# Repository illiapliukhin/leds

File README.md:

# leds

LED matrix / wearable LED electronics, firmware and tools.

## Where things live
- **mono_electronics v15 (ESP32-S3 mono LED driver board, PR #4): standalone KiCad project, fab outputs, drawings, renders and docs in [`projects/mono_electronics_v15/`](projects/mono_electronics_v15/).** This is the canonical copy to open and order from.
- Working sources: `hardware/mono_schematic/` (schematic and generator tools), `hardware/mono_electronics/` (board, review docs); fab history in `manufacturing/mono_electronics/` (v11b–v15).
- Interface standard: `hardware/common/LED_INTERFACE_STANDARD.md`.
- Firmware: `firmware/`. Simulators and analysis: `tools/`, `leds_analysis/`.

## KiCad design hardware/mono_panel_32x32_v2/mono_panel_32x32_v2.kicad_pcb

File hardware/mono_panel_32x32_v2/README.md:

# mono_panel_32x32_v2 — 32×32 white 2835 LED panel, 8 mm pitch, 256×256 mm

This is a single-colour matrix panel for `projects/mono_electronics_v15`, following `hardware/common/LED_INTERFACE_STANDARD.md`.
- J_ROW1 and J_COL1 are Hirose FH12-40S-0.5SH on B.Cu, mid-board. Pin 1 is north; the cable exits west when viewed from the back. Use a 40-way 0.5 mm FFC, Type B (pin 1 → pin 1), ≤200 mm.
- J_ROW: 35/36 ID_SDA/SCL, 37 ID_3V3, 33/38/39/40 GND, 34 NC.
- U_ID1 is an M24C02 EEPROM at address 0x50.
- Six M2 NPTH holes, 2.2 mm (use nylon screws/standoffs). Fiducials 3 + 3.
- Edge-to-first-LED distance is 4.0 mm = pitch/2, so panels tile edge-to-edge with a continuous 8 mm pitch.
- See TRADE_STUDY.md for the LED choice and cost.

| Gate (KiCad 10.0.7) | Result |
|---|---|
| ERC (all severities) | 0 |
| DRC (all severities) | 0 |
| Unconnected | 0 |
| Schematic parity | 0 |

Rules (in `.kicad_pro`) and stackup:
- 0.127 mm minimum clearance; tracks ≥0.15 mm; vias 0.6/0.3; edge 0.3 mm.
- Stackup JLC04161H-7628, 1.6 mm, 1 oz outer.
- Every bend is a tangent arc: router output is string-pulled to any-angle straight runs (bilinear distance-field line of sight, 0.15 mm clearance), then filleted; `check_bends.py` audits tangency. GND zones on In2/B.Cu use thermal reliefs (0.3 gap / 0.3 spoke) and are refilled before plotting. 455 GND stitching vias.

## Row drop (docs/analysis.json, from the routed copper)
- Load: 32 LEDs × 10 mA = 0.32 A per row.
- Copper: ρ +20% (60 °C / plating). The bus is modelled as distributed load fed from the worst end.
- Worst case is ROW_01:
  - board ≈ 75 mV (1.0 mm bus ≈ 0.46 Ω/2, plus fan-out and via)
  - plus 200 mm FFC 1.64 Ω/m and 2 contacts ≈ 124 mV
  - **total ≈ 199 mV, under the 350 mV budget.**
- Worst-case headroom: 4.24 − 0.199 − 0.035 (AO3403) − 2.75 V (Vf max) ≈ 1.26 V left for the MBI5124 sink.
- IPC-2221 at ΔT 10 °C: 0.3 mm external ≈ 1.0 A; 1.0 mm bus ≈ 2.4 A; 0.2 mm internal ≈ 0.37 A.
  - These compare against 0.32 A peak / 57 mA RMS (1/32 duty), so heating is negligible.

## Build
- `./build.sh`: schematic → PCB base → maze router → arcs/zones → ERC/DRC/parity.
- `./make_fab.sh`: zone refill, gerbers + drill, `fab/BOM_JLC.csv`, `fab/CPL_JLC.csv`, zip.
- `python3.11 analyze.py`: row-drop analysis.

## JLC
- Upload `fab/mono_panel_32x32_v2_gerbers.zip`: 4 layers, 1.6 mm, impedance stackup JLC04161H-7628.
- PCBA both sides, using BOM_JLC.csv and CPL_JLC.csv.
- Parts: C2843876 ×1024, C202114 ×2, C7562, C1525. All were in stock on 2026-10-12.

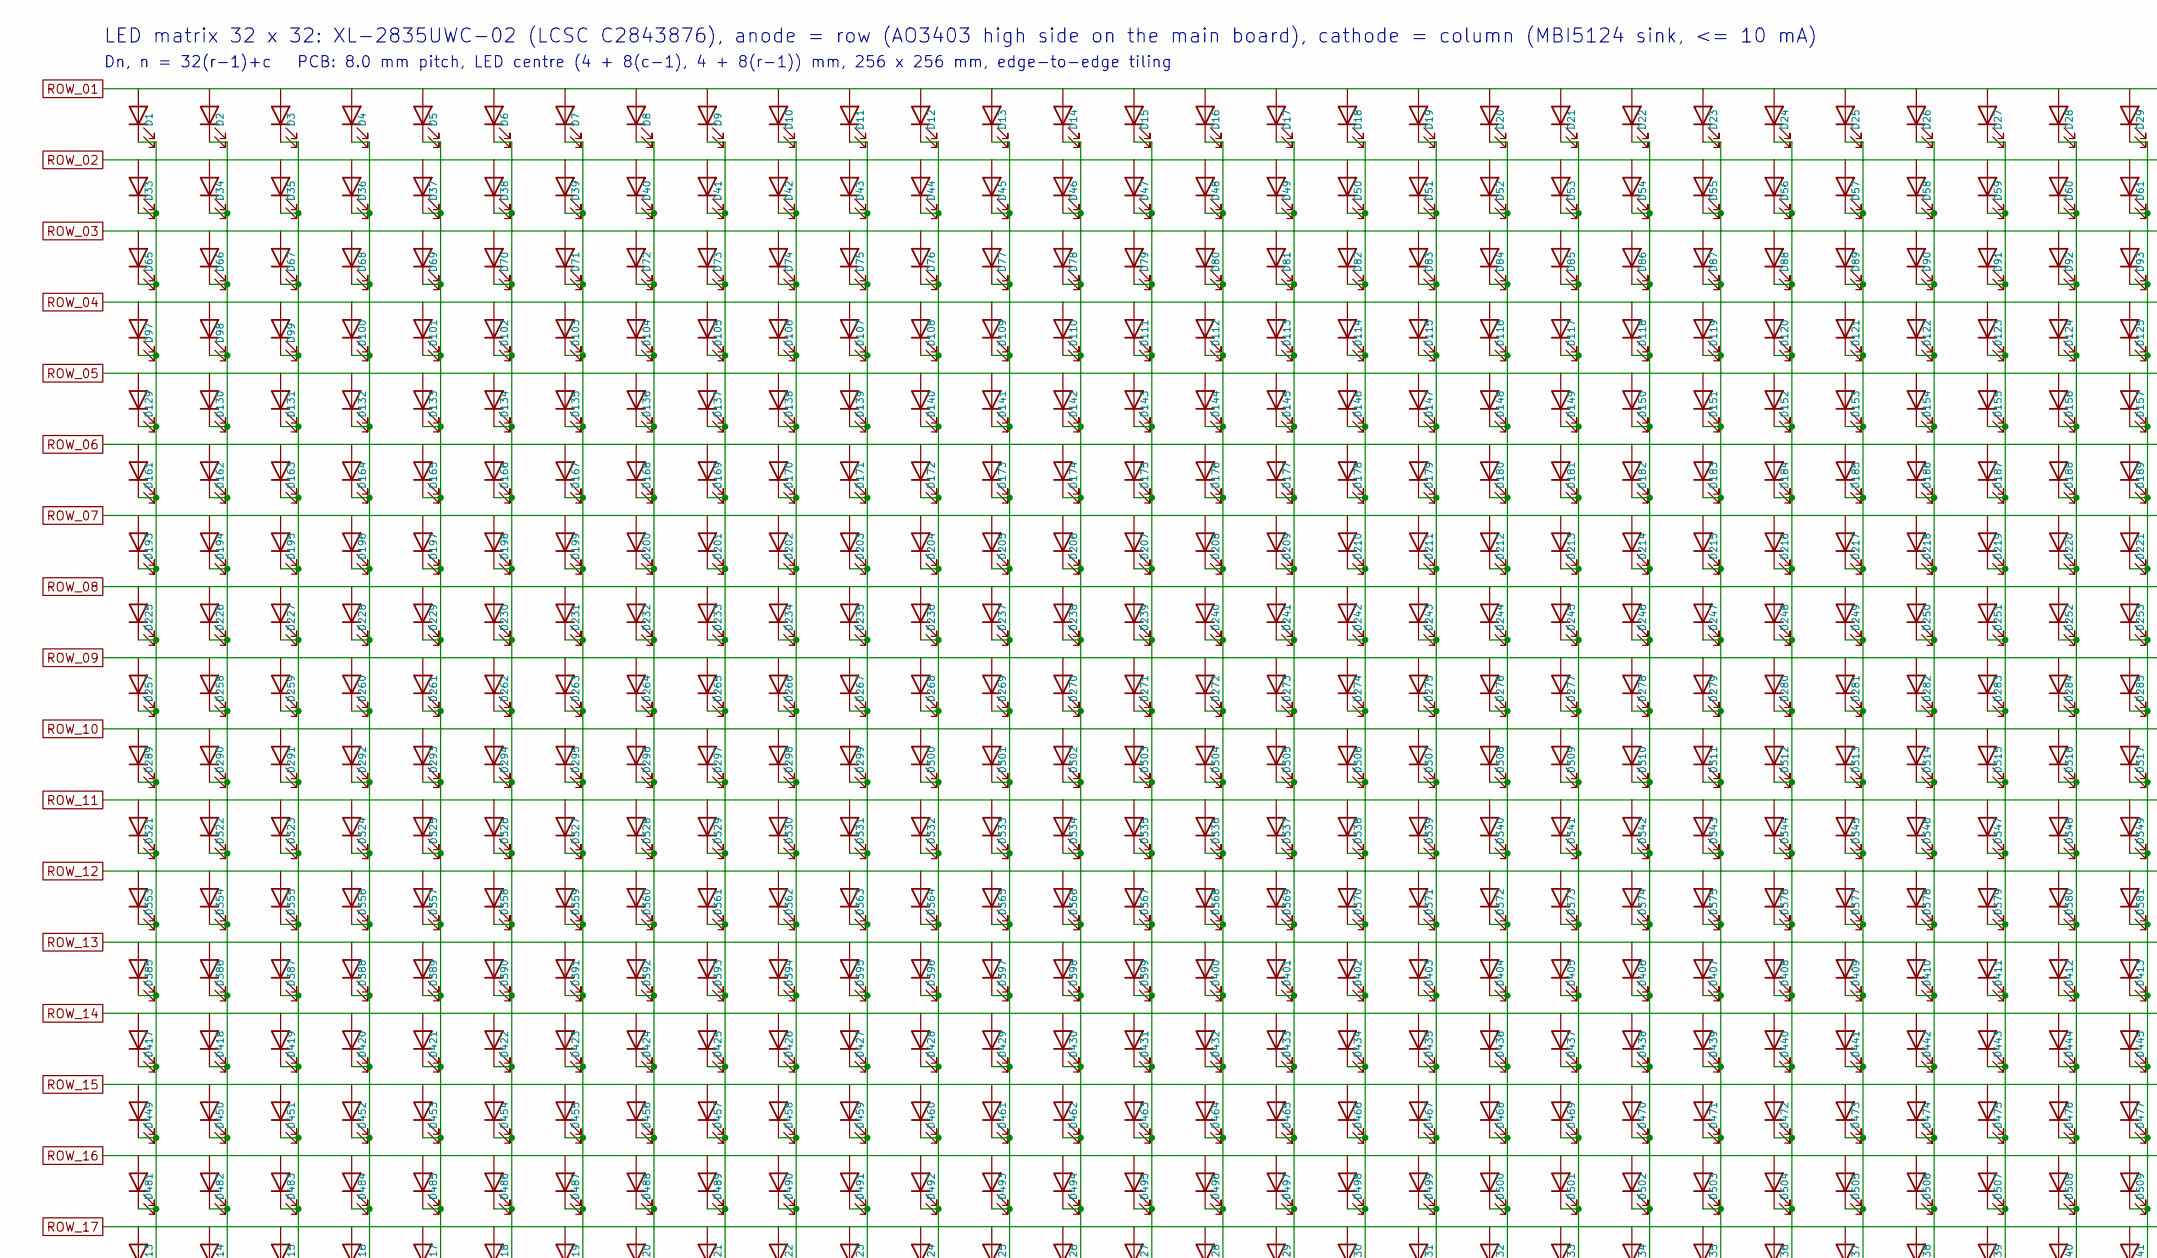
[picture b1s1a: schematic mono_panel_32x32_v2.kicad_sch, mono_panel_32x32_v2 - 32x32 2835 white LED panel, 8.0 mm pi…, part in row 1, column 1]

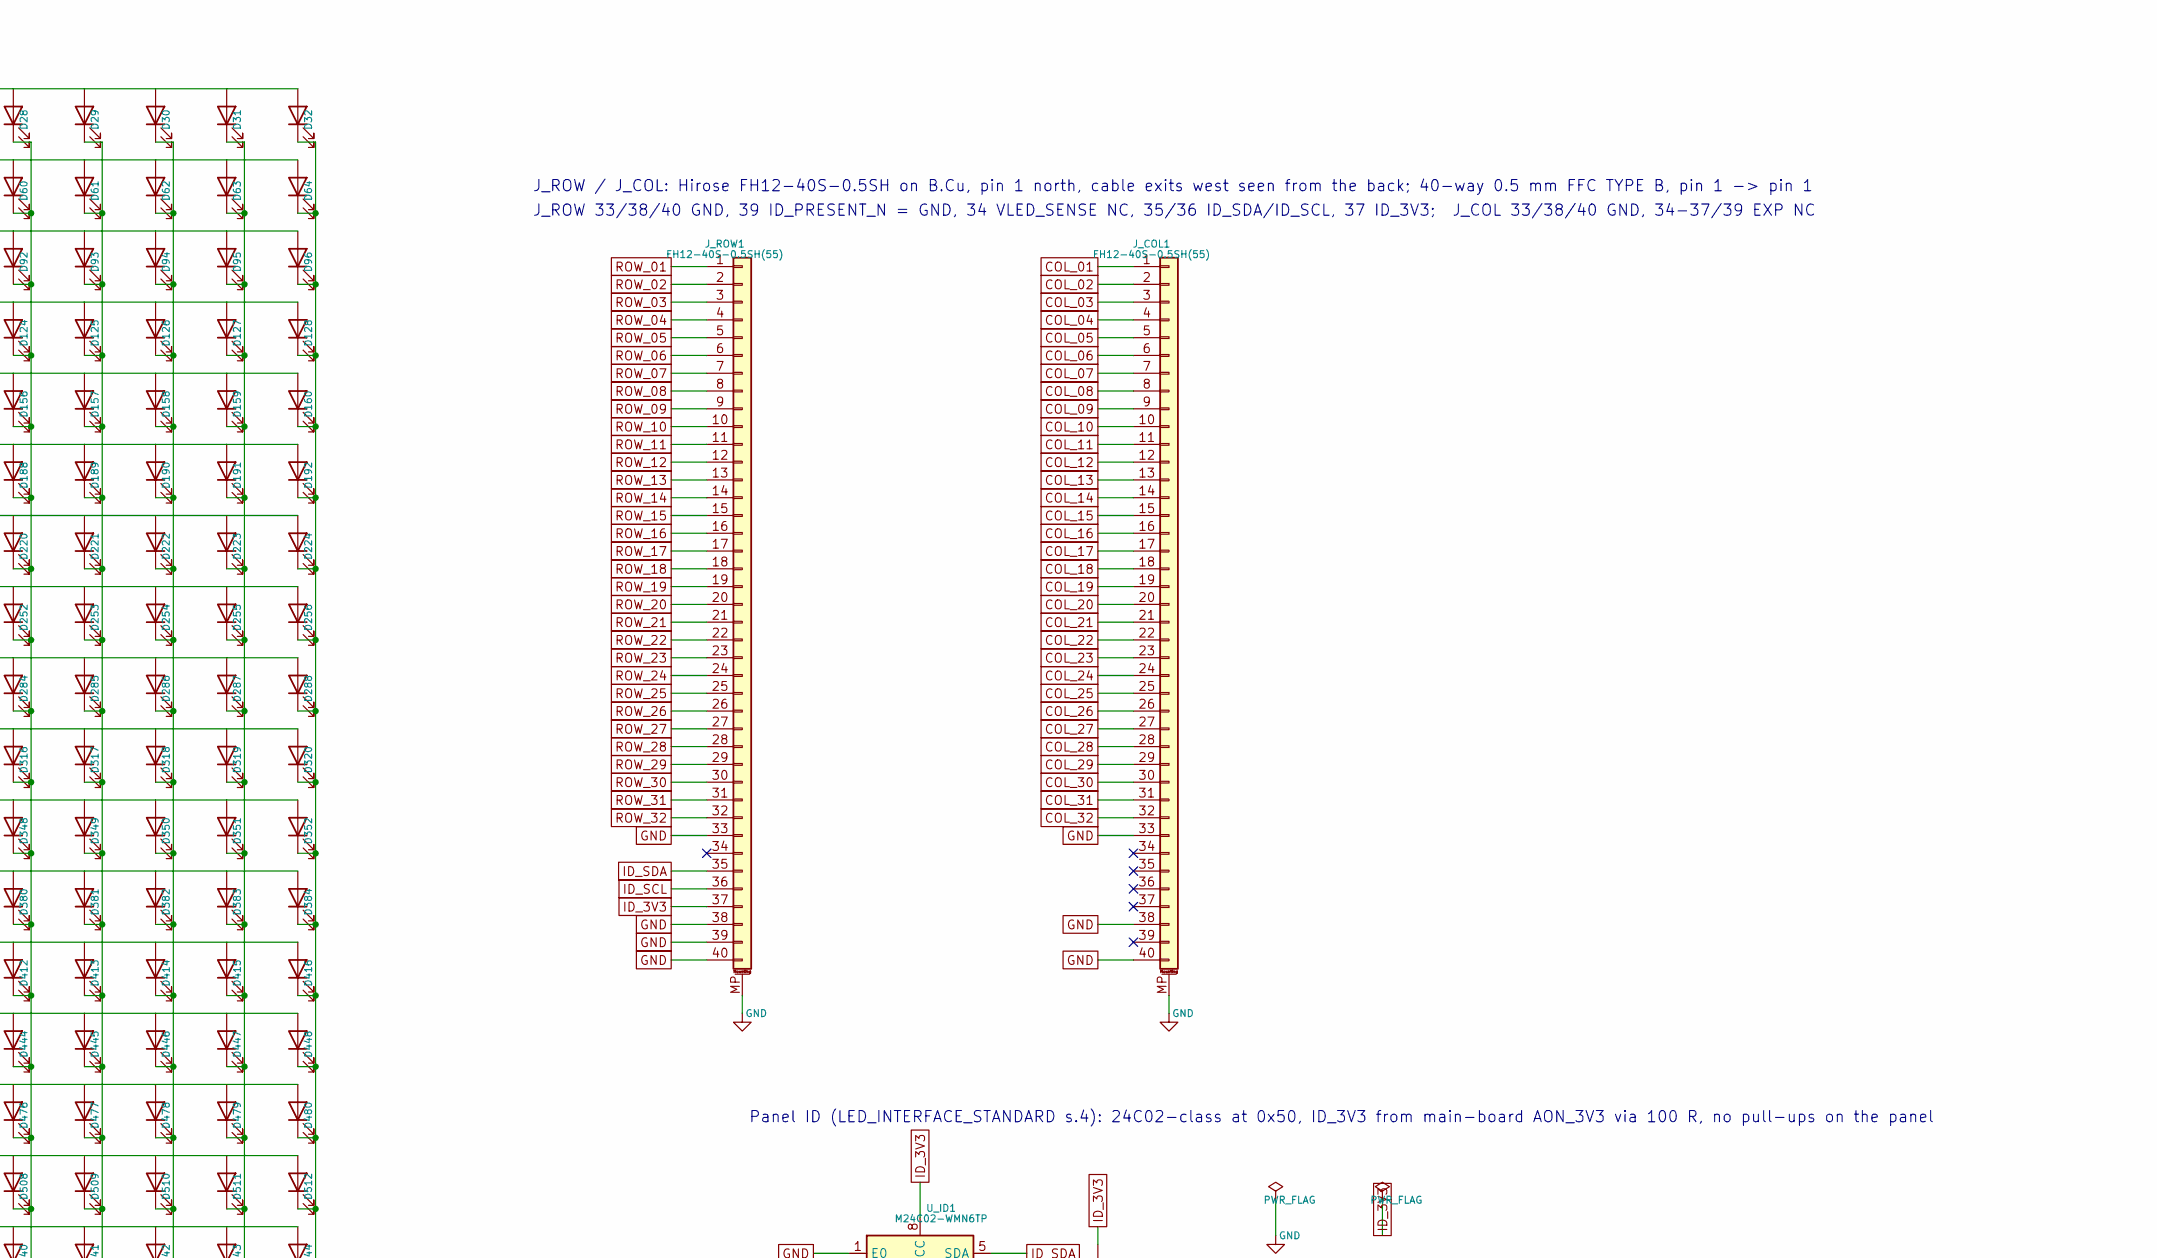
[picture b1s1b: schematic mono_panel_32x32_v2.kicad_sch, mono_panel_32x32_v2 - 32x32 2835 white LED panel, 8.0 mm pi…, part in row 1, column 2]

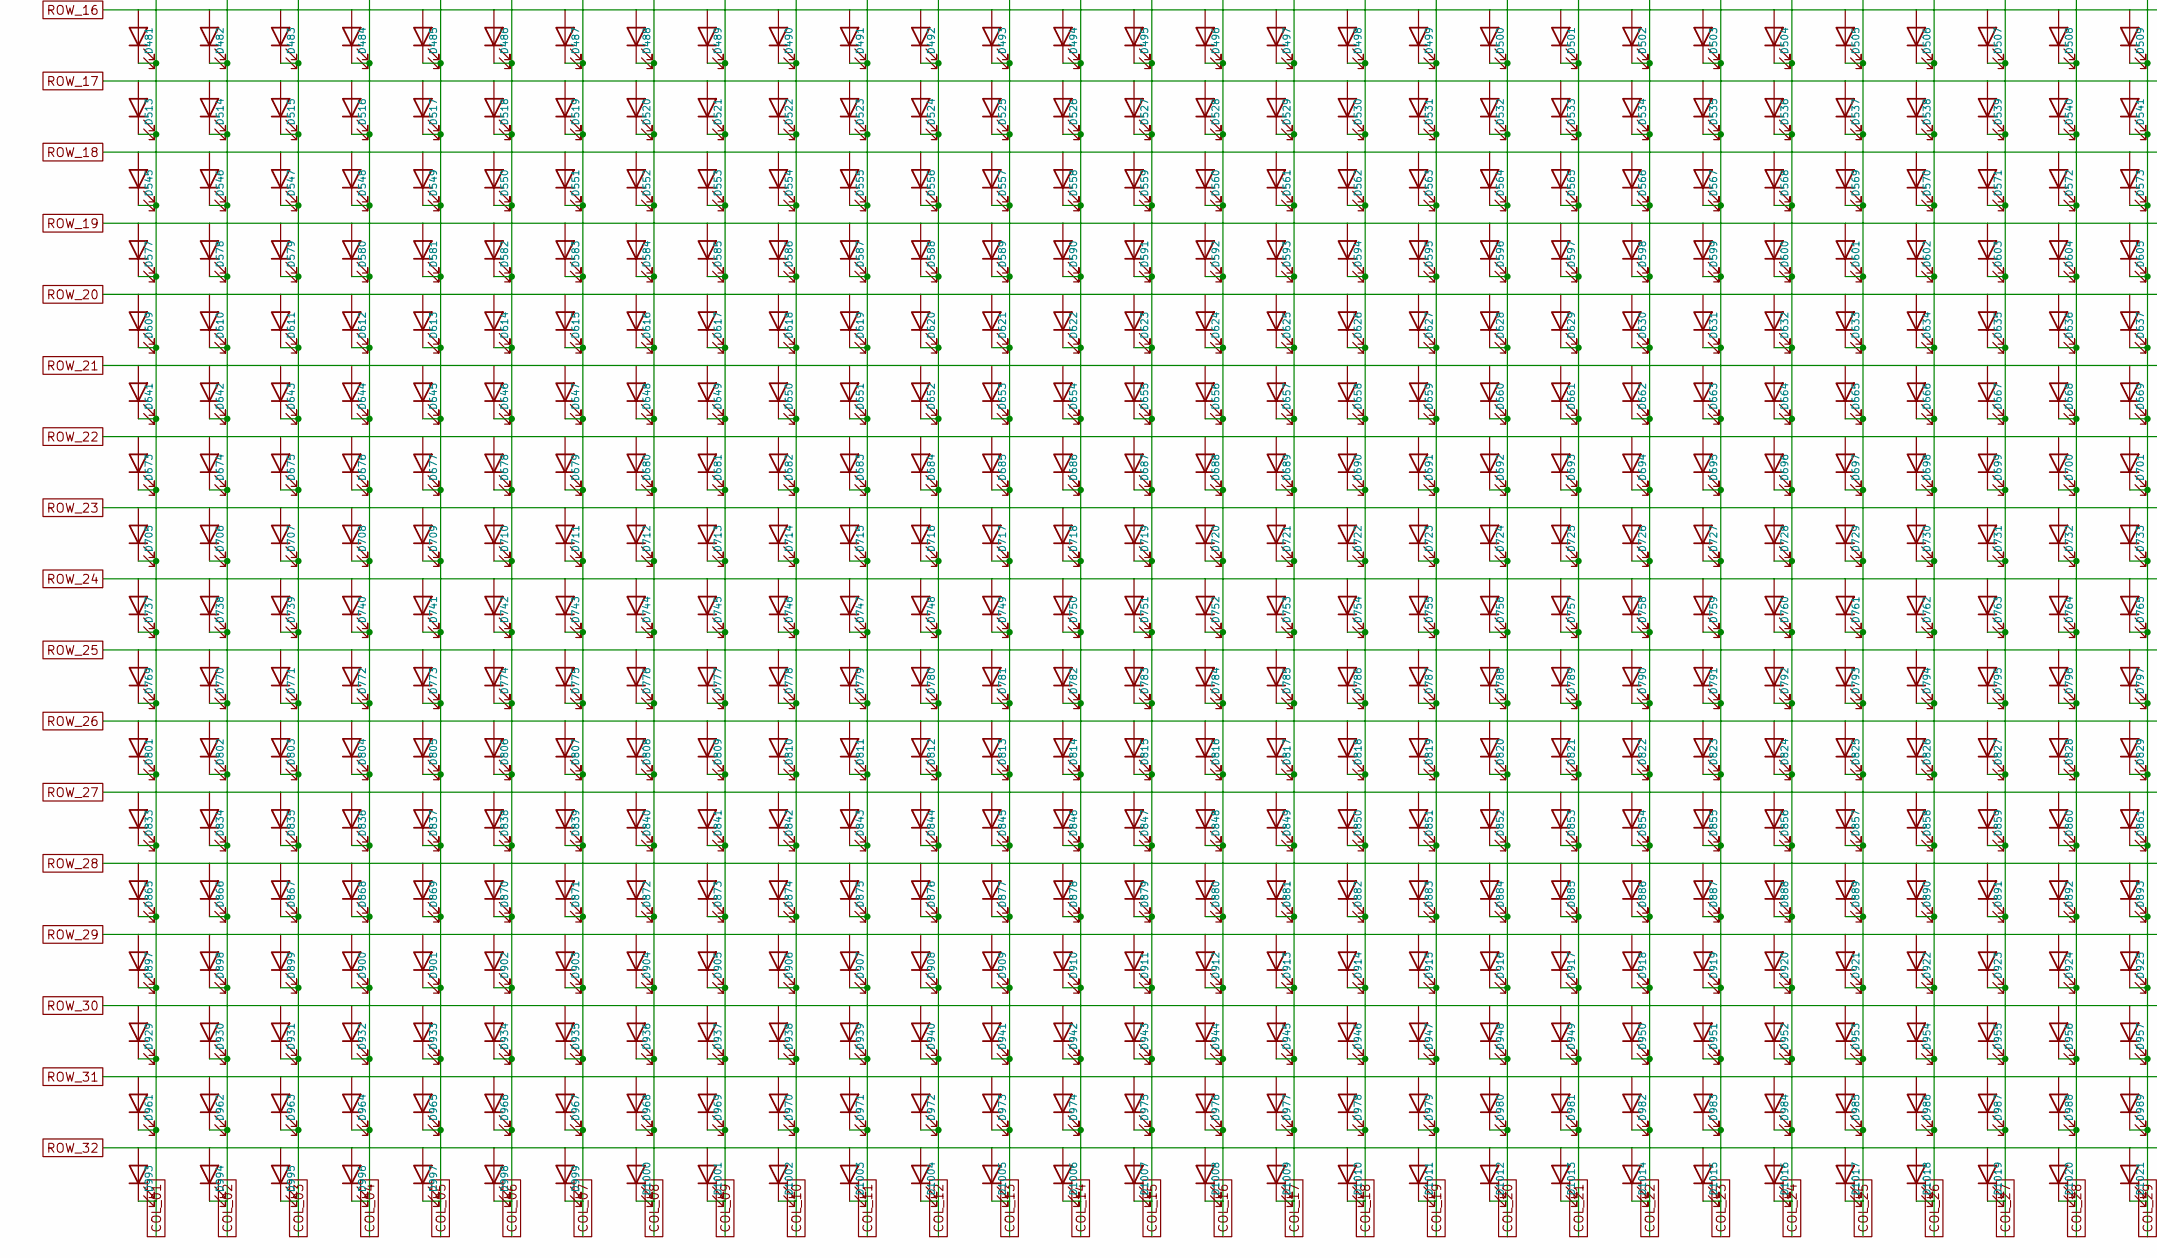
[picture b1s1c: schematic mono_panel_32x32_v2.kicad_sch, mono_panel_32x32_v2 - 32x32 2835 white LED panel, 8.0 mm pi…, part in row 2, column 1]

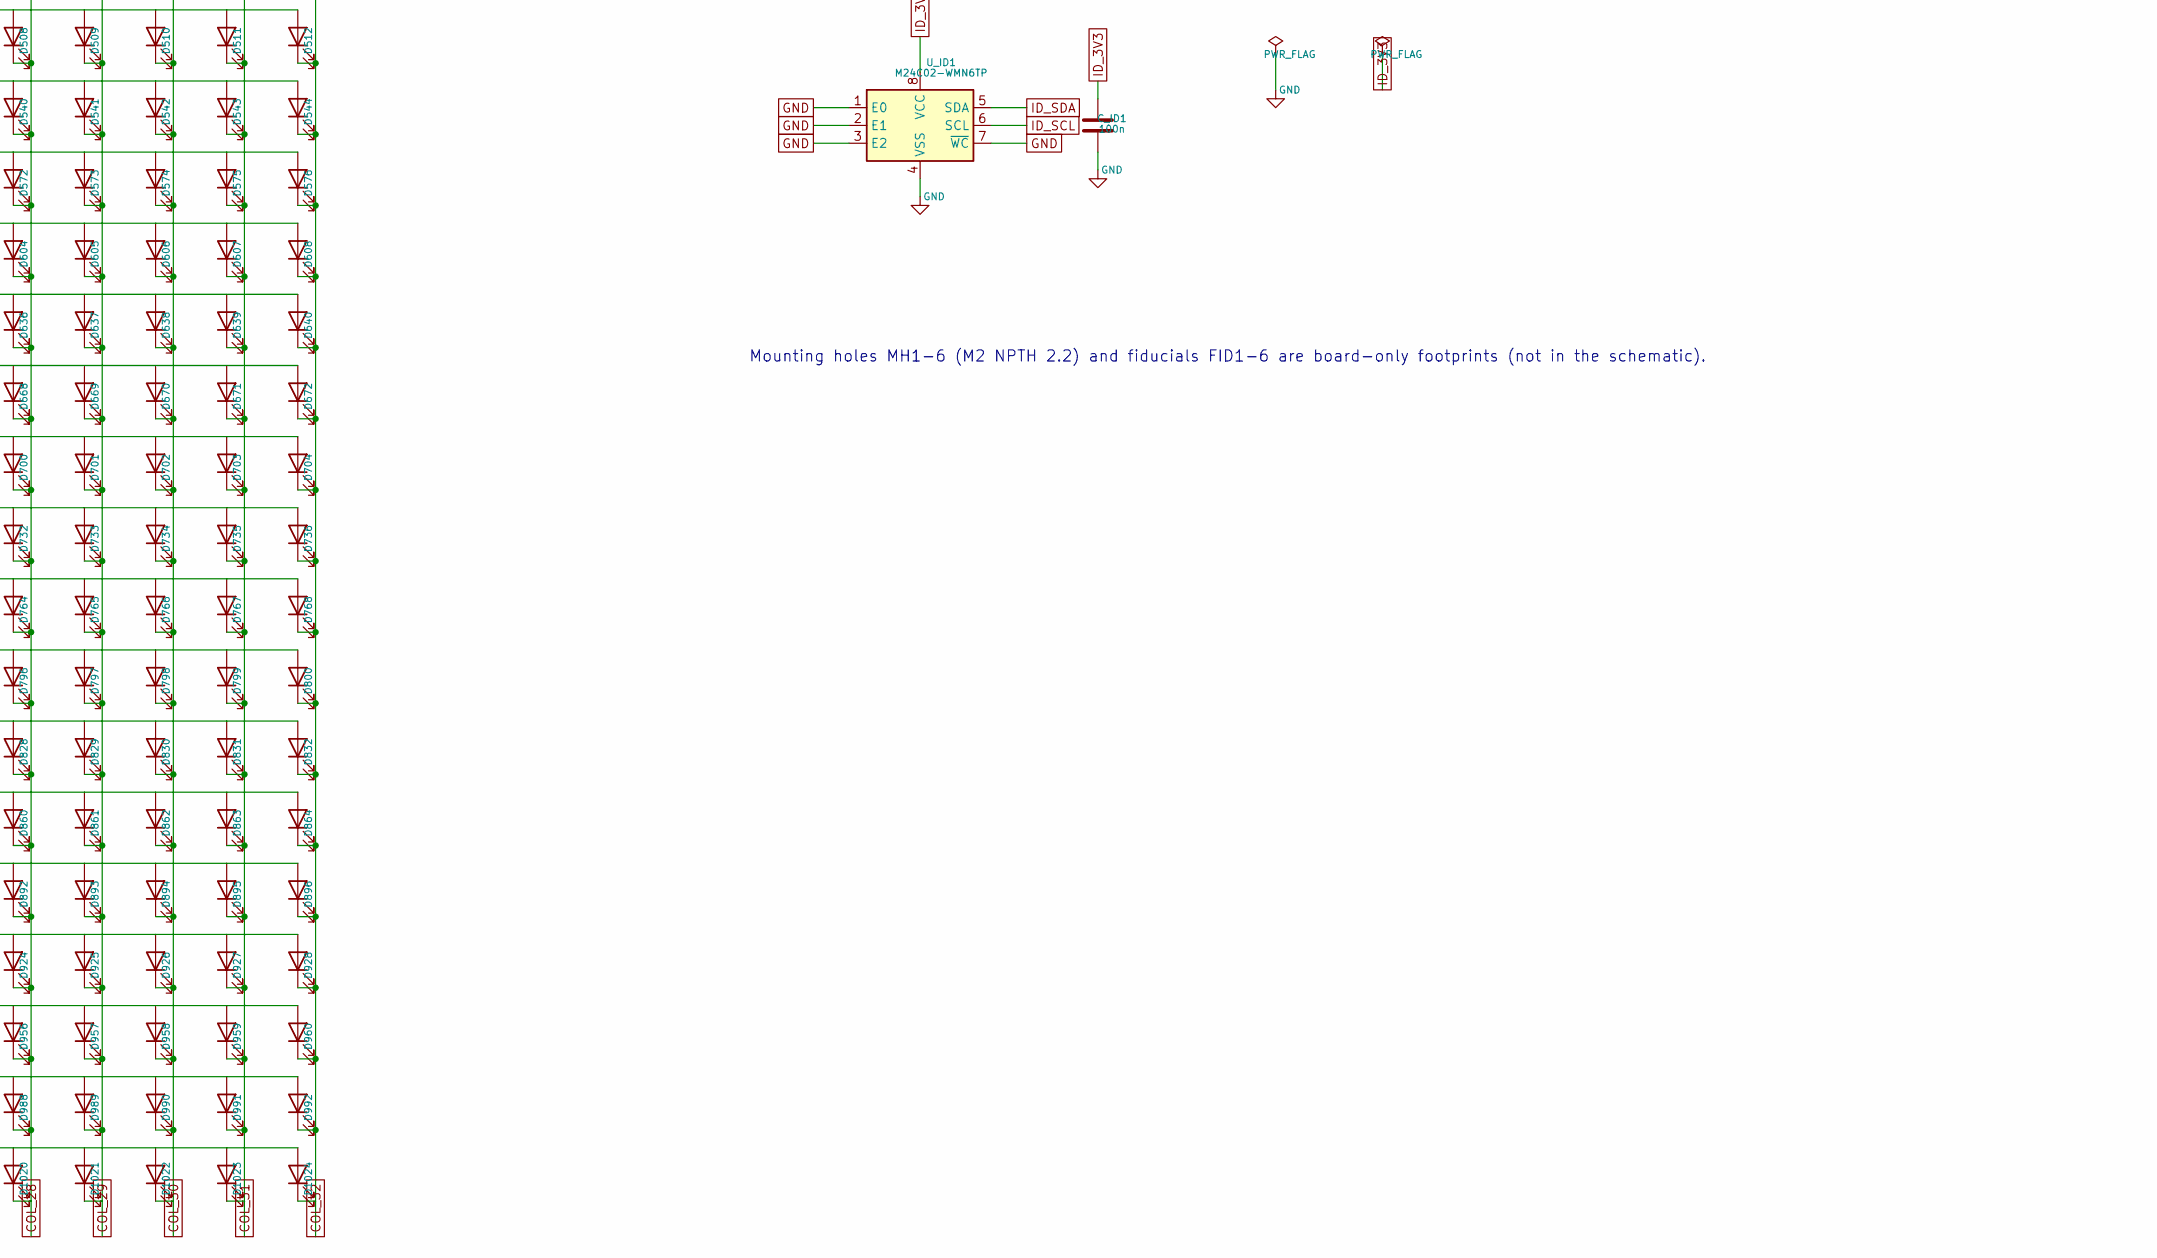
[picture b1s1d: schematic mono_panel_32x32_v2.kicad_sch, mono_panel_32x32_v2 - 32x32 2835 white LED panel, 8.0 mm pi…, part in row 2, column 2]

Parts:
C_ID1: 100n; C_0402_1005Metric; MPN Samsung CL05B104KO5NNNC; LCSC C1525
D1, D2, D3, D4, D5, D6, D7, D8, D9, D10, D11, D12, D13, D14, D15, D16, D17, D18, D19, D20, D21, D22, D23, D24, D25, D26, D27, D28, D29, D30, D31, D32, D33, D34, D35, D36, D37, D38, D39, D40, D41, D42, D43, D44, D45, D46, D47, D48, D49, D50, D51, D52, D53, D54, D55, D56, D57, D58, D59, D60, D61, D62, D63, D64, D65, D66, D67, D68, D69, D70, D71, D72, D73, D74, D75, D76, D77, D78, D79, D80, D81, D82, D83, D84, D85, D86, D87, D88, D89, D90, D91, D92, D93, D94, D95, D96, D97, D98, D99, D100, D101, D102, D103, D104, D105, D106, D107, D108, D109, D110, D111, D112, D113, D114, D115, D116, D117, D118, D119, D120, D121, D122, D123, D124, D125, D126, D127, D128, D129, D130, D131, D132, D133, D134, D135, D136, D137, D138, D139, D140, D141, D142, D143, D144, D145, D146, D147, D148, D149, D150, D151, D152, D153, D154, D155, D156, D157, D158, D159, D160, D161, D162, D163, D164, D165, D166, D167, D168, D169, D170, D171, D172, D173, D174, D175, D176, D177, D178, D179, D180, D181, D182, D183, D184, D185, D186, D187, D188, D189, D190, D191, D192, D193, D194, D195, D196, D197, D198, D199, D200, D201, D202, D203, D204, D205, D206, D207, D208, D209, D210, D211, D212, D213, D214, D215, D216, D217, D218, D219, D220, D221, D222, D223, D224, D225, D226, D227, D228, D229, D230, D231, D232, D233, D234, D235, D236, D237, D238, D239, D240, D241, D242, D243, D244, D245, D246, D247, D248, D249, D250, D251, D252, D253, D254, D255, D256, D257, D258, D259, D260, D261, D262, D263, D264, D265, D266, D267, D268, D269, D270, D271, D272, D273, D274, D275, D276, D277, D278, D279, D280, D281, D282, D283, D284, D285, D286, D287, D288, D289, D290, D291, D292, D293, D294, D295, D296, D297, D298, D299, D300, D301, D302, D303, D304, D305, D306, D307, D308, D309, D310, D311, D312, D313, D314, D315, D316, D317, D318, D319, D320, D321, D322, D323, D324, D325, D326, D327, D328, D329, D330, D331, D332, D333, D334, D335, D336, D337, D338, D339, D340, D341, D342, D343, D344, D345, D346, D347, D348, D349, D350, D351, D352, D353, D354, D355, D356, D357, D358, D359, D360, D361, D362, D363, D364, D365, D366, D367, D368, D369, D370, D371, D372, D373, D374, D375, D376, D377, D378, D379, D380, D381, D382, D383, D384, D385, D386, D387, D388, D389, D390, D391, D392, D393, D394, D395, D396, D397, D398, D399, D400, D401, D402, D403, D404, D405, D406, D407, D408, D409, D410, D411, D412, D413, D414, D415, D416, D417, D418, D419, D420, D421, D422, D423, D424, D425, D426, D427, D428, D429, D430, D431, D432, D433, D434, D435, D436, D437, D438, D439, D440, D441, D442, D443, D444, D445, D446, D447, D448, D449, D450, D451, D452, D453, D454, D455, D456, D457, D458, D459, D460, D461, D462, D463, D464, D465, D466, D467, D468, D469, D470, D471, D472, D473, D474, D475, D476, D477, D478, D479, D480, D481, D482, D483, D484, D485, D486, D487, D488, D489, D490, D491, D492, D493, D494, D495, D496, D497, D498, D499, D500, D501, D502, D503, D504, D505, D506, D507, D508, D509, D510, D511, D512, D513, D514, D515, D516, D517, D518, D519, D520, D521, D522, D523, D524, D525, D526, D527, D528, D529, D530, D531, D532, D533, D534, D535, D536, D537, D538, D539, D540, D541, D542, D543, D544, D545, D546, D547, D548, D549, D550, D551, D552, D553, D554, D555, D556, D557, D558, D559, D560, D561, D562, D563, D564, D565, D566, D567, D568, D569, D570, D571, D572, D573, D574, D575, D576, D577, D578, D579, D580, D581, D582, D583, D584, D585, D586, D587, D588, D589, D590, D591, D592, D593, D594, D595, D596, D597, D598, D599, D600, D601, D602, D603, D604, D605, D606, D607, D608, D609, D610, D611, D612, D613, D614, D615, D616, D617, D618, D619, D620, D621, D622, D623, D624, D625, D626, D627, D628, D629, D630, D631, D632, D633, D634, D635, D636, D637, D638, D639, D640, D641, D642, D643, D644, D645, D646, D647, D648, D649, D650, D651, D652, D653, D654, D655, D656, D657, D658, D659, D660, D661, D662, D663, D664, D665, D666, D667, D668, D669, D670, D671, D672, D673, D674, D675, D676, D677, D678, D679, D680, D681, D682, D683, D684, D685, D686, D687, D688, D689, D690, D691, D692, D693, D694, D695, D696, D697, D698, D699, D700, D701, D702, D703, D704, D705, D706, D707, D708, D709, D710, D711, D712, D713, D714, D715, D716, D717, D718, D719, D720, D721, D722, D723, D724, D725, D726, D727, D728, D729, D730, D731, D732, D733, D734, D735, D736, D737, D738, D739, D740, D741, D742, D743, D744, D745, D746, D747, D748, D749, D750, D751, D752, D753, D754, D755, D756, D757, D758, D759, D760, D761, D762, D763, D764, D765, D766, D767, D768, D769, D770, D771, D772, D773, D774, D775, D776, D777, D778, D779, D780, D781, D782, D783, D784, D785, D786, D787, D788, D789, D790, D791, D792, D793, D794, D795, D796, D797, D798, D799, D800, D801, D802, D803, D804, D805, D806, D807, D808, D809, D810, D811, D812, D813, D814, D815, D816, D817, D818, D819, D820, D821, D822, D823, D824, D825, D826, D827, D828, D829, D830, D831, D832, D833, D834, D835, D836, D837, D838, D839, D840, D841, D842, D843, D844, D845, D846, D847, D848, D849, D850, D851, D852, D853, D854, D855, D856, D857, D858, D859, D860, D861, D862, D863, D864, D865, D866, D867, D868, D869, D870, D871, D872, D873, D874, D875, D876, D877, D878, D879, D880, D881, D882, D883, D884, D885, D886, D887, D888, D889, D890, D891, D892, D893, D894, D895, D896, D897, D898, D899, D900, D901, D902, D903, D904, D905, D906, D907, D908, D909, D910, D911, D912, D913, D914, D915, D916, D917, D918, D919, D920, D921, D922, D923, D924, D925, D926, D927, D928, D929, D930, D931, D932, D933, D934, D935, D936, D937, D938, D939, D940, D941, D942, D943, D944, D945, D946, D947, D948, D949, D950, D951, D952, D953, D954, D955, D956, D957, D958, D959, D960, D961, D962, D963, D964, D965, D966, D967, D968, D969, D970, D971, D972, D973, D974, D975, D976, D977, D978, D979, D980, D981, D982, D983, D984, D985, D986, D987, D988, D989, D990, D991, D992, D993, D994, D995, D996, D997, D998, D999, D1000, D1001, D1002, D1003, D1004, D1005, D1006, D1007, D1008, D1009, D1010, D1011, D1012, D1013, D1014, D1015, D1016, D1017, D1018, D1019, D1020, D1021, D1022, D1023, D1024: XL-2835UWC-02; LED_2835_XL-2835UWC; MPN XINGLIGHT XL-2835UWC-02; LCSC C2843876
J_COL1: FH12-40S-0.5SH(55); Hirose_FH12-40S-0.5SH_B; MPN Hirose FH12-40S-0.5SH(55); LCSC C202114
J_ROW1: FH12-40S-0.5SH(55); Hirose_FH12-40S-0.5SH_B; MPN Hirose FH12-40S-0.5SH(55); LCSC C202114
U_ID1: M24C02-WMN6TP; SOIC-8_3.9x4.9mm_P1.27mm; MPN ST M24C02-WMN6TP; LCSC C7562

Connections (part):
COL_01: D1.1 (K), D33.1 (K), D65.1 (K), D97.1 (K), D129.1 (K), D161.1 (K), D193.1 (K), D225.1 (K), D257.1 (K), D289.1 (K), D321.1 (K), D353.1 (K), D385.1 (K), D417.1 (K), D449.1 (K), D481.1 (K), D513.1 (K), D545.1 (K), D577.1 (K), D609.1 (K), D641.1 (K), D673.1 (K), D705.1 (K), D737.1 (K), D769.1 (K), D801.1 (K), D833.1 (K), D865.1 (K), D897.1 (K), D929.1 (K), D961.1 (K), D993.1 (K), J_COL1.1
COL_02: D2.1 (K), D34.1 (K), D66.1 (K), D98.1 (K), D130.1 (K), D162.1 (K), D194.1 (K), D226.1 (K), D258.1 (K), D290.1 (K), D322.1 (K), D354.1 (K), D386.1 (K), D418.1 (K), D450.1 (K), D482.1 (K), D514.1 (K), D546.1 (K), D578.1 (K), D610.1 (K), D642.1 (K), D674.1 (K), D706.1 (K), D738.1 (K), D770.1 (K), D802.1 (K), D834.1 (K), D866.1 (K), D898.1 (K), D930.1 (K), D962.1 (K), D994.1 (K), J_COL1.2
COL_03: D3.1 (K), D35.1 (K), D67.1 (K), D99.1 (K), D131.1 (K), D163.1 (K), D195.1 (K), D227.1 (K), D259.1 (K), D291.1 (K), D323.1 (K), D355.1 (K), D387.1 (K), D419.1 (K), D451.1 (K), D483.1 (K), D515.1 (K), D547.1 (K), D579.1 (K), D611.1 (K), D643.1 (K), D675.1 (K), D707.1 (K), D739.1 (K), D771.1 (K), D803.1 (K), D835.1 (K), D867.1 (K), D899.1 (K), D931.1 (K), D963.1 (K), D995.1 (K), J_COL1.3
COL_04: D4.1 (K), D36.1 (K), D68.1 (K), D100.1 (K), D132.1 (K), D164.1 (K), D196.1 (K), D228.1 (K), D260.1 (K), D292.1 (K), D324.1 (K), D356.1 (K), D388.1 (K), D420.1 (K), D452.1 (K), D484.1 (K), D516.1 (K), D548.1 (K), D580.1 (K), D612.1 (K), D644.1 (K), D676.1 (K), D708.1 (K), D740.1 (K), D772.1 (K), D804.1 (K), D836.1 (K), D868.1 (K), D900.1 (K), D932.1 (K), D964.1 (K), D996.1 (K), J_COL1.4
COL_05: D5.1 (K), D37.1 (K), D69.1 (K), D101.1 (K), D133.1 (K), D165.1 (K), D197.1 (K), D229.1 (K), D261.1 (K), D293.1 (K), D325.1 (K), D357.1 (K), D389.1 (K), D421.1 (K), D453.1 (K), D485.1 (K), D517.1 (K), D549.1 (K), D581.1 (K), D613.1 (K), D645.1 (K), D677.1 (K), D709.1 (K), D741.1 (K), D773.1 (K), D805.1 (K), D837.1 (K), D869.1 (K), D901.1 (K), D933.1 (K), D965.1 (K), D997.1 (K), J_COL1.5
COL_06: D6.1 (K), D38.1 (K), D70.1 (K), D102.1 (K), D134.1 (K), D166.1 (K), D198.1 (K), D230.1 (K), D262.1 (K), D294.1 (K), D326.1 (K), D358.1 (K), D390.1 (K), D422.1 (K), D454.1 (K), D486.1 (K), D518.1 (K), D550.1 (K), D582.1 (K), D614.1 (K), D646.1 (K), D678.1 (K), D710.1 (K), D742.1 (K), D774.1 (K), D806.1 (K), D838.1 (K), D870.1 (K), D902.1 (K), D934.1 (K), D966.1 (K), D998.1 (K), J_COL1.6
COL_07: D7.1 (K), D39.1 (K), D71.1 (K), D103.1 (K), D135.1 (K), D167.1 (K), D199.1 (K), D231.1 (K), D263.1 (K), D295.1 (K), D327.1 (K), D359.1 (K), D391.1 (K), D423.1 (K), D455.1 (K), D487.1 (K), D519.1 (K), D551.1 (K), D583.1 (K), D615.1 (K), D647.1 (K), D679.1 (K), D711.1 (K), D743.1 (K), D775.1 (K), D807.1 (K), D839.1 (K), D871.1 (K), D903.1 (K), D935.1 (K), D967.1 (K), D999.1 (K), J_COL1.7
COL_08: D8.1 (K), D40.1 (K), D72.1 (K), D104.1 (K), D136.1 (K), D168.1 (K), D200.1 (K), D232.1 (K), D264.1 (K), D296.1 (K), D328.1 (K), D360.1 (K), D392.1 (K), D424.1 (K), D456.1 (K), D488.1 (K), D520.1 (K), D552.1 (K), D584.1 (K), D616.1 (K), D648.1 (K), D680.1 (K), D712.1 (K), D744.1 (K), D776.1 (K), D808.1 (K), D840.1 (K), D872.1 (K), D904.1 (K), D936.1 (K), D968.1 (K), D1000.1 (K), J_COL1.8
COL_09: D9.1 (K), D41.1 (K), D73.1 (K), D105.1 (K), D137.1 (K), D169.1 (K), D201.1 (K), D233.1 (K), D265.1 (K), D297.1 (K), D329.1 (K), D361.1 (K), D393.1 (K), D425.1 (K), D457.1 (K), D489.1 (K), D521.1 (K), D553.1 (K), D585.1 (K), D617.1 (K), D649.1 (K), D681.1 (K), D713.1 (K), D745.1 (K), D777.1 (K), D809.1 (K), D841.1 (K), D873.1 (K), D905.1 (K), D937.1 (K), D969.1 (K), D1001.1 (K), J_COL1.9
COL_10: D10.1 (K), D42.1 (K), D74.1 (K), D106.1 (K), D138.1 (K), D170.1 (K), D202.1 (K), D234.1 (K), D266.1 (K), D298.1 (K), D330.1 (K), D362.1 (K), D394.1 (K), D426.1 (K), D458.1 (K), D490.1 (K), D522.1 (K), D554.1 (K), D586.1 (K), D618.1 (K), D650.1 (K), D682.1 (K), D714.1 (K), D746.1 (K), D778.1 (K), D810.1 (K), D842.1 (K), D874.1 (K), D906.1 (K), D938.1 (K), D970.1 (K), D1002.1 (K), J_COL1.10
COL_11: D11.1 (K), D43.1 (K), D75.1 (K), D107.1 (K), D139.1 (K), D171.1 (K), D203.1 (K), D235.1 (K), D267.1 (K), D299.1 (K), D331.1 (K), D363.1 (K), D395.1 (K), D427.1 (K), D459.1 (K), D491.1 (K), D523.1 (K), D555.1 (K), D587.1 (K), D619.1 (K), D651.1 (K), D683.1 (K), D715.1 (K), D747.1 (K), D779.1 (K), D811.1 (K), D843.1 (K), D875.1 (K), D907.1 (K), D939.1 (K), D971.1 (K), D1003.1 (K), J_COL1.11
COL_12: D12.1 (K), D44.1 (K), D76.1 (K), D108.1 (K), D140.1 (K), D172.1 (K), D204.1 (K), D236.1 (K), D268.1 (K), D300.1 (K), D332.1 (K), D364.1 (K), D396.1 (K), D428.1 (K), D460.1 (K), D492.1 (K), D524.1 (K), D556.1 (K), D588.1 (K), D620.1 (K), D652.1 (K), D684.1 (K), D716.1 (K), D748.1 (K), D780.1 (K), D812.1 (K), D844.1 (K), D876.1 (K), D908.1 (K), D940.1 (K), D972.1 (K), D1004.1 (K), J_COL1.12
COL_13: D13.1 (K), D45.1 (K), D77.1 (K), D109.1 (K), D141.1 (K), D173.1 (K), D205.1 (K), D237.1 (K), D269.1 (K), D301.1 (K), D333.1 (K), D365.1 (K), D397.1 (K), D429.1 (K), D461.1 (K), D493.1 (K), D525.1 (K), D557.1 (K), D589.1 (K), D621.1 (K), D653.1 (K), D685.1 (K), D717.1 (K), D749.1 (K), D781.1 (K), D813.1 (K), D845.1 (K), D877.1 (K), D909.1 (K), D941.1 (K), D973.1 (K), D1005.1 (K), J_COL1.13
COL_14: D14.1 (K), D46.1 (K), D78.1 (K), D110.1 (K), D142.1 (K), D174.1 (K), D206.1 (K), D238.1 (K), D270.1 (K), D302.1 (K), D334.1 (K), D366.1 (K), D398.1 (K), D430.1 (K), D462.1 (K), D494.1 (K), D526.1 (K), D558.1 (K), D590.1 (K), D622.1 (K), D654.1 (K), D686.1 (K), D718.1 (K), D750.1 (K), D782.1 (K), D814.1 (K), D846.1 (K), D878.1 (K), D910.1 (K), D942.1 (K), D974.1 (K), D1006.1 (K), J_COL1.14
COL_15: D15.1 (K), D47.1 (K), D79.1 (K), D111.1 (K), D143.1 (K), D175.1 (K), D207.1 (K), D239.1 (K), D271.1 (K), D303.1 (K), D335.1 (K), D367.1 (K), D399.1 (K), D431.1 (K), D463.1 (K), D495.1 (K), D527.1 (K), D559.1 (K), D591.1 (K), D623.1 (K), D655.1 (K), D687.1 (K), D719.1 (K), D751.1 (K), D783.1 (K), D815.1 (K), D847.1 (K), D879.1 (K), D911.1 (K), D943.1 (K), D975.1 (K), D1007.1 (K), J_COL1.15
COL_16: D16.1 (K), D48.1 (K), D80.1 (K), D112.1 (K), D144.1 (K), D176.1 (K), D208.1 (K), D240.1 (K), D272.1 (K), D304.1 (K), D336.1 (K), D368.1 (K), D400.1 (K), D432.1 (K), D464.1 (K), D496.1 (K), D528.1 (K), D560.1 (K), D592.1 (K), D624.1 (K), D656.1 (K), D688.1 (K), D720.1 (K), D752.1 (K), D784.1 (K), D816.1 (K), D848.1 (K), D880.1 (K), D912.1 (K), D944.1 (K), D976.1 (K), D1008.1 (K), J_COL1.16
COL_17: D17.1 (K), D49.1 (K), D81.1 (K), D113.1 (K), D145.1 (K), D177.1 (K), D209.1 (K), D241.1 (K), D273.1 (K), D305.1 (K), D337.1 (K), D369.1 (K), D401.1 (K), D433.1 (K), D465.1 (K), D497.1 (K), D529.1 (K), D561.1 (K), D593.1 (K), D625.1 (K), D657.1 (K), D689.1 (K), D721.1 (K), D753.1 (K), D785.1 (K), D817.1 (K), D849.1 (K), D881.1 (K), D913.1 (K), D945.1 (K), D977.1 (K), D1009.1 (K), J_COL1.17
COL_18: D18.1 (K), D50.1 (K), D82.1 (K), D114.1 (K), D146.1 (K), D178.1 (K), D210.1 (K), D242.1 (K), D274.1 (K), D306.1 (K), D338.1 (K), D370.1 (K), D402.1 (K), D434.1 (K), D466.1 (K), D498.1 (K), D530.1 (K), D562.1 (K), D594.1 (K), D626.1 (K), D658.1 (K), D690.1 (K), D722.1 (K), D754.1 (K), D786.1 (K), D818.1 (K), D850.1 (K), D882.1 (K), D914.1 (K), D946.1 (K), D978.1 (K), D1010.1 (K), J_COL1.18
COL_19: D19.1 (K), D51.1 (K), D83.1 (K), D115.1 (K), D147.1 (K), D179.1 (K), D211.1 (K), D243.1 (K), D275.1 (K), D307.1 (K), D339.1 (K), D371.1 (K), D403.1 (K), D435.1 (K), D467.1 (K), D499.1 (K), D531.1 (K), D563.1 (K), D595.1 (K), D627.1 (K), D659.1 (K), D691.1 (K), D723.1 (K), D755.1 (K), D787.1 (K), D819.1 (K), D851.1 (K), D883.1 (K), D915.1 (K), D947.1 (K), D979.1 (K), D1011.1 (K), J_COL1.19
COL_20: D20.1 (K), D52.1 (K), D84.1 (K), D116.1 (K), D148.1 (K), D180.1 (K), D212.1 (K), D244.1 (K), D276.1 (K), D308.1 (K), D340.1 (K), D372.1 (K), D404.1 (K), D436.1 (K), D468.1 (K), D500.1 (K), D532.1 (K), D564.1 (K), D596.1 (K), D628.1 (K), D660.1 (K), D692.1 (K), D724.1 (K), D756.1 (K), D788.1 (K), D820.1 (K), D852.1 (K), D884.1 (K), D916.1 (K), D948.1 (K), D980.1 (K), D1012.1 (K), J_COL1.20
COL_21: D21.1 (K), D53.1 (K), D85.1 (K), D117.1 (K), D149.1 (K), D181.1 (K), D213.1 (K), D245.1 (K), D277.1 (K), D309.1 (K), D341.1 (K), D373.1 (K), D405.1 (K), D437.1 (K), D469.1 (K), D501.1 (K), D533.1 (K), D565.1 (K), D597.1 (K), D629.1 (K), D661.1 (K), D693.1 (K), D725.1 (K), D757.1 (K), D789.1 (K), D821.1 (K), D853.1 (K), D885.1 (K), D917.1 (K), D949.1 (K), D981.1 (K), D1013.1 (K), J_COL1.21
COL_22: D22.1 (K), D54.1 (K), D86.1 (K), D118.1 (K), D150.1 (K), D182.1 (K), D214.1 (K), D246.1 (K), D278.1 (K), D310.1 (K), D342.1 (K), D374.1 (K), D406.1 (K), D438.1 (K), D470.1 (K), D502.1 (K), D534.1 (K), D566.1 (K), D598.1 (K), D630.1 (K), D662.1 (K), D694.1 (K), D726.1 (K), D758.1 (K), D790.1 (K), D822.1 (K), D854.1 (K), D886.1 (K), D918.1 (K), D950.1 (K), D982.1 (K), D1014.1 (K), J_COL1.22
COL_23: D23.1 (K), D55.1 (K), D87.1 (K), D119.1 (K), D151.1 (K), D183.1 (K), D215.1 (K), D247.1 (K), D279.1 (K), D311.1 (K), D343.1 (K), D375.1 (K), D407.1 (K), D439.1 (K), D471.1 (K), D503.1 (K), D535.1 (K), D567.1 (K), D599.1 (K), D631.1 (K), D663.1 (K), D695.1 (K), D727.1 (K), D759.1 (K), D791.1 (K), D823.1 (K), D855.1 (K), D887.1 (K), D919.1 (K), D951.1 (K), D983.1 (K), D1015.1 (K), J_COL1.23
COL_24: D24.1 (K), D56.1 (K), D88.1 (K), D120.1 (K), D152.1 (K), D184.1 (K), D216.1 (K), D248.1 (K), D280.1 (K), D312.1 (K), D344.1 (K), D376.1 (K), D408.1 (K), D440.1 (K), D472.1 (K), D504.1 (K), D536.1 (K), D568.1 (K), D600.1 (K), D632.1 (K), D664.1 (K), D696.1 (K), D728.1 (K), D760.1 (K), D792.1 (K), D824.1 (K), D856.1 (K), D888.1 (K), D920.1 (K), D952.1 (K), D984.1 (K), D1016.1 (K), J_COL1.24
COL_25: D25.1 (K), D57.1 (K), D89.1 (K), D121.1 (K), D153.1 (K), D185.1 (K), D217.1 (K), D249.1 (K), D281.1 (K), D313.1 (K), D345.1 (K), D377.1 (K), D409.1 (K), D441.1 (K), D473.1 (K), D505.1 (K), D537.1 (K), D569.1 (K), D601.1 (K), D633.1 (K), D665.1 (K), D697.1 (K), D729.1 (K), D761.1 (K), D793.1 (K), D825.1 (K), D857.1 (K), D889.1 (K), D921.1 (K), D953.1 (K), D985.1 (K), D1017.1 (K), J_COL1.25
COL_26: D26.1 (K), D58.1 (K), D90.1 (K), D122.1 (K), D154.1 (K), D186.1 (K), D218.1 (K), D250.1 (K), D282.1 (K), D314.1 (K), D346.1 (K), D378.1 (K), D410.1 (K), D442.1 (K), D474.1 (K), D506.1 (K), D538.1 (K), D570.1 (K), D602.1 (K), D634.1 (K), D666.1 (K), D698.1 (K), D730.1 (K), D762.1 (K), D794.1 (K), D826.1 (K), D858.1 (K), D890.1 (K), D922.1 (K), D954.1 (K), D986.1 (K), D1018.1 (K), J_COL1.26
COL_27: D27.1 (K), D59.1 (K), D91.1 (K), D123.1 (K), D155.1 (K), D187.1 (K), D219.1 (K), D251.1 (K), D283.1 (K), D315.1 (K), D347.1 (K), D379.1 (K), D411.1 (K), D443.1 (K), D475.1 (K), D507.1 (K), D539.1 (K), D571.1 (K), D603.1 (K), D635.1 (K), D667.1 (K), D699.1 (K), D731.1 (K), D763.1 (K), D795.1 (K), D827.1 (K), D859.1 (K), D891.1 (K), D923.1 (K), D955.1 (K), D987.1 (K), D1019.1 (K), J_COL1.27
COL_28: D28.1 (K), D60.1 (K), D92.1 (K), D124.1 (K), D156.1 (K), D188.1 (K), D220.1 (K), D252.1 (K), D284.1 (K), D316.1 (K), D348.1 (K), D380.1 (K), D412.1 (K), D444.1 (K), D476.1 (K), D508.1 (K), D540.1 (K), D572.1 (K), D604.1 (K), D636.1 (K), D668.1 (K), D700.1 (K), D732.1 (K), D764.1 (K), D796.1 (K), D828.1 (K), D860.1 (K), D892.1 (K), D924.1 (K), D956.1 (K), D988.1 (K), D1020.1 (K), J_COL1.28
COL_29: D29.1 (K), D61.1 (K), D93.1 (K), D125.1 (K), D157.1 (K), D189.1 (K), D221.1 (K), D253.1 (K), D285.1 (K), D317.1 (K), D349.1 (K), D381.1 (K), D413.1 (K), D445.1 (K), D477.1 (K), D509.1 (K), D541.1 (K), D573.1 (K), D605.1 (K), D637.1 (K), D669.1 (K), D701.1 (K), D733.1 (K), D765.1 (K), D797.1 (K), D829.1 (K), D861.1 (K), D893.1 (K), D925.1 (K), D957.1 (K), D989.1 (K), D1021.1 (K), J_COL1.29
COL_30: D30.1 (K), D62.1 (K), D94.1 (K), D126.1 (K), D158.1 (K), D190.1 (K), D222.1 (K), D254.1 (K), D286.1 (K), D318.1 (K), D350.1 (K), D382.1 (K), D414.1 (K), D446.1 (K), D478.1 (K), D510.1 (K), D542.1 (K), D574.1 (K), D606.1 (K), D638.1 (K), D670.1 (K), D702.1 (K), D734.1 (K), D766.1 (K), D798.1 (K), D830.1 (K), D862.1 (K), D894.1 (K), D926.1 (K), D958.1 (K), D990.1 (K), D1022.1 (K), J_COL1.30
COL_31: D31.1 (K), D63.1 (K), D95.1 (K), D127.1 (K), D159.1 (K), D191.1 (K), D223.1 (K), D255.1 (K), D287.1 (K), D319.1 (K), D351.1 (K), D383.1 (K), D415.1 (K), D447.1 (K), D479.1 (K), D511.1 (K), D543.1 (K), D575.1 (K), D607.1 (K), D639.1 (K), D671.1 (K), D703.1 (K), D735.1 (K), D767.1 (K), D799.1 (K), D831.1 (K), D863.1 (K), D895.1 (K), D927.1 (K), D959.1 (K), D991.1 (K), D1023.1 (K), J_COL1.31
COL_32: D32.1 (K), D64.1 (K), D96.1 (K), D128.1 (K), D160.1 (K), D192.1 (K), D224.1 (K), D256.1 (K), D288.1 (K), D320.1 (K), D352.1 (K), D384.1 (K), D416.1 (K), D448.1 (K), D480.1 (K), D512.1 (K), D544.1 (K), D576.1 (K), D608.1 (K), D640.1 (K), D672.1 (K), D704.1 (K), D736.1 (K), D768.1 (K), D800.1 (K), D832.1 (K), D864.1 (K), D896.1 (K), D928.1 (K), D960.1 (K), D992.1 (K), D1024.1 (K), J_COL1.32
GND: C_ID1.2, J_COL1.33, J_COL1.38, J_COL1.40, J_COL1.MP (MountPin), J_ROW1.33, J_ROW1.38, J_ROW1.39, J_ROW1.40, J_ROW1.MP (MountPin), U_ID1.1 (E0), U_ID1.2 (E1), U_ID1.3 (E2), U_ID1.4 (VSS), U_ID1.7 (~WC)
ID_3V3: C_ID1.1, J_ROW1.37, U_ID1.8 (VCC)
ID_SCL: J_ROW1.36, U_ID1.6 (SCL)
ID_SDA: J_ROW1.35, U_ID1.5 (SDA)
ROW_01: D1.2 (A), D2.2 (A), D3.2 (A), D4.2 (A), D5.2 (A), D6.2 (A), D7.2 (A), D8.2 (A), D9.2 (A), D10.2 (A), D11.2 (A), D12.2 (A), D13.2 (A), D14.2 (A), D15.2 (A), D16.2 (A), D17.2 (A), D18.2 (A), D19.2 (A), D20.2 (A), D21.2 (A), D22.2 (A), D23.2 (A), D24.2 (A), D25.2 (A), D26.2 (A), D27.2 (A), D28.2 (A), D29.2 (A), D30.2 (A), D31.2 (A), D32.2 (A), J_ROW1.1
ROW_02: D33.2 (A), D34.2 (A), D35.2 (A), D36.2 (A), D37.2 (A), D38.2 (A), D39.2 (A), D40.2 (A), D41.2 (A), D42.2 (A), D43.2 (A), D44.2 (A), D45.2 (A), D46.2 (A), D47.2 (A), D48.2 (A), D49.2 (A), D50.2 (A), D51.2 (A), D52.2 (A), D53.2 (A), D54.2 (A), D55.2 (A), D56.2 (A), D57.2 (A), D58.2 (A), D59.2 (A), D60.2 (A), D61.2 (A), D62.2 (A), D63.2 (A), D64.2 (A), J_ROW1.2
ROW_03: D65.2 (A), D66.2 (A), D67.2 (A), D68.2 (A), D69.2 (A), D70.2 (A), D71.2 (A), D72.2 (A), D73.2 (A), D74.2 (A), D75.2 (A), D76.2 (A), D77.2 (A), D78.2 (A), D79.2 (A), D80.2 (A), D81.2 (A), D82.2 (A), D83.2 (A), D84.2 (A), D85.2 (A), D86.2 (A), D87.2 (A), D88.2 (A), D89.2 (A), D90.2 (A), D91.2 (A), D92.2 (A), D93.2 (A), D94.2 (A), D95.2 (A), D96.2 (A), J_ROW1.3
ROW_04: D97.2 (A), D98.2 (A), D99.2 (A), D100.2 (A), D101.2 (A), D102.2 (A), D103.2 (A), D104.2 (A), D105.2 (A), D106.2 (A), D107.2 (A), D108.2 (A), D109.2 (A), D110.2 (A), D111.2 (A), D112.2 (A), D113.2 (A), D114.2 (A), D115.2 (A), D116.2 (A), D117.2 (A), D118.2 (A), D119.2 (A), D120.2 (A), D121.2 (A), D122.2 (A), D123.2 (A), D124.2 (A), D125.2 (A), D126.2 (A), D127.2 (A), D128.2 (A), J_ROW1.4
ROW_05: D129.2 (A), D130.2 (A), D131.2 (A), D132.2 (A), D133.2 (A), D134.2 (A), D135.2 (A), D136.2 (A), D137.2 (A), D138.2 (A), D139.2 (A), D140.2 (A), D141.2 (A), D142.2 (A), D143.2 (A), D144.2 (A), D145.2 (A), D146.2 (A), D147.2 (A), D148.2 (A), D149.2 (A), D150.2 (A), D151.2 (A), D152.2 (A), D153.2 (A), D154.2 (A), D155.2 (A), D156.2 (A), D157.2 (A), D158.2 (A), D159.2 (A), D160.2 (A), J_ROW1.5
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
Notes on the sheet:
LED matrix 32 x 32: XL-2835UWC-02 (LCSC C2843876), anode = row (AO3403 high side on the main board), cathode = column (MBI5124 sink, <= 10 mA)
Dn, n = 32(r-1)+c PCB: 8.0 mm pitch, LED centre (4 + 8(c-1), 4 + 8(r-1)) mm, 256 x 256 mm, edge-to-edge tiling
J_ROW / J_COL: Hirose FH12-40S-0.5SH on B.Cu, pin 1 north, cable exits west seen from the back; 40-way 0.5 mm FFC TYPE B, pin 1 -> pin 1
J_ROW 33/38/40 GND, 39 ID_PRESENT_N = GND, 34 VLED_SENSE NC, 35/36 ID_SDA/ID_SCL, 37 ID_3V3; J_COL 33/38/40 GND, 34-37/39 EXP NC
Panel ID (LED_INTERFACE_STANDARD s.4): 24C02-class at 0x50, ID_3V3 from main-board AON_3V3 via 100 R, no pull-ups on the panel
Mounting holes MH1-6 (M2 NPTH 2.2) and fiducials FID1-6 are board-only footprints (not in the schematic).
